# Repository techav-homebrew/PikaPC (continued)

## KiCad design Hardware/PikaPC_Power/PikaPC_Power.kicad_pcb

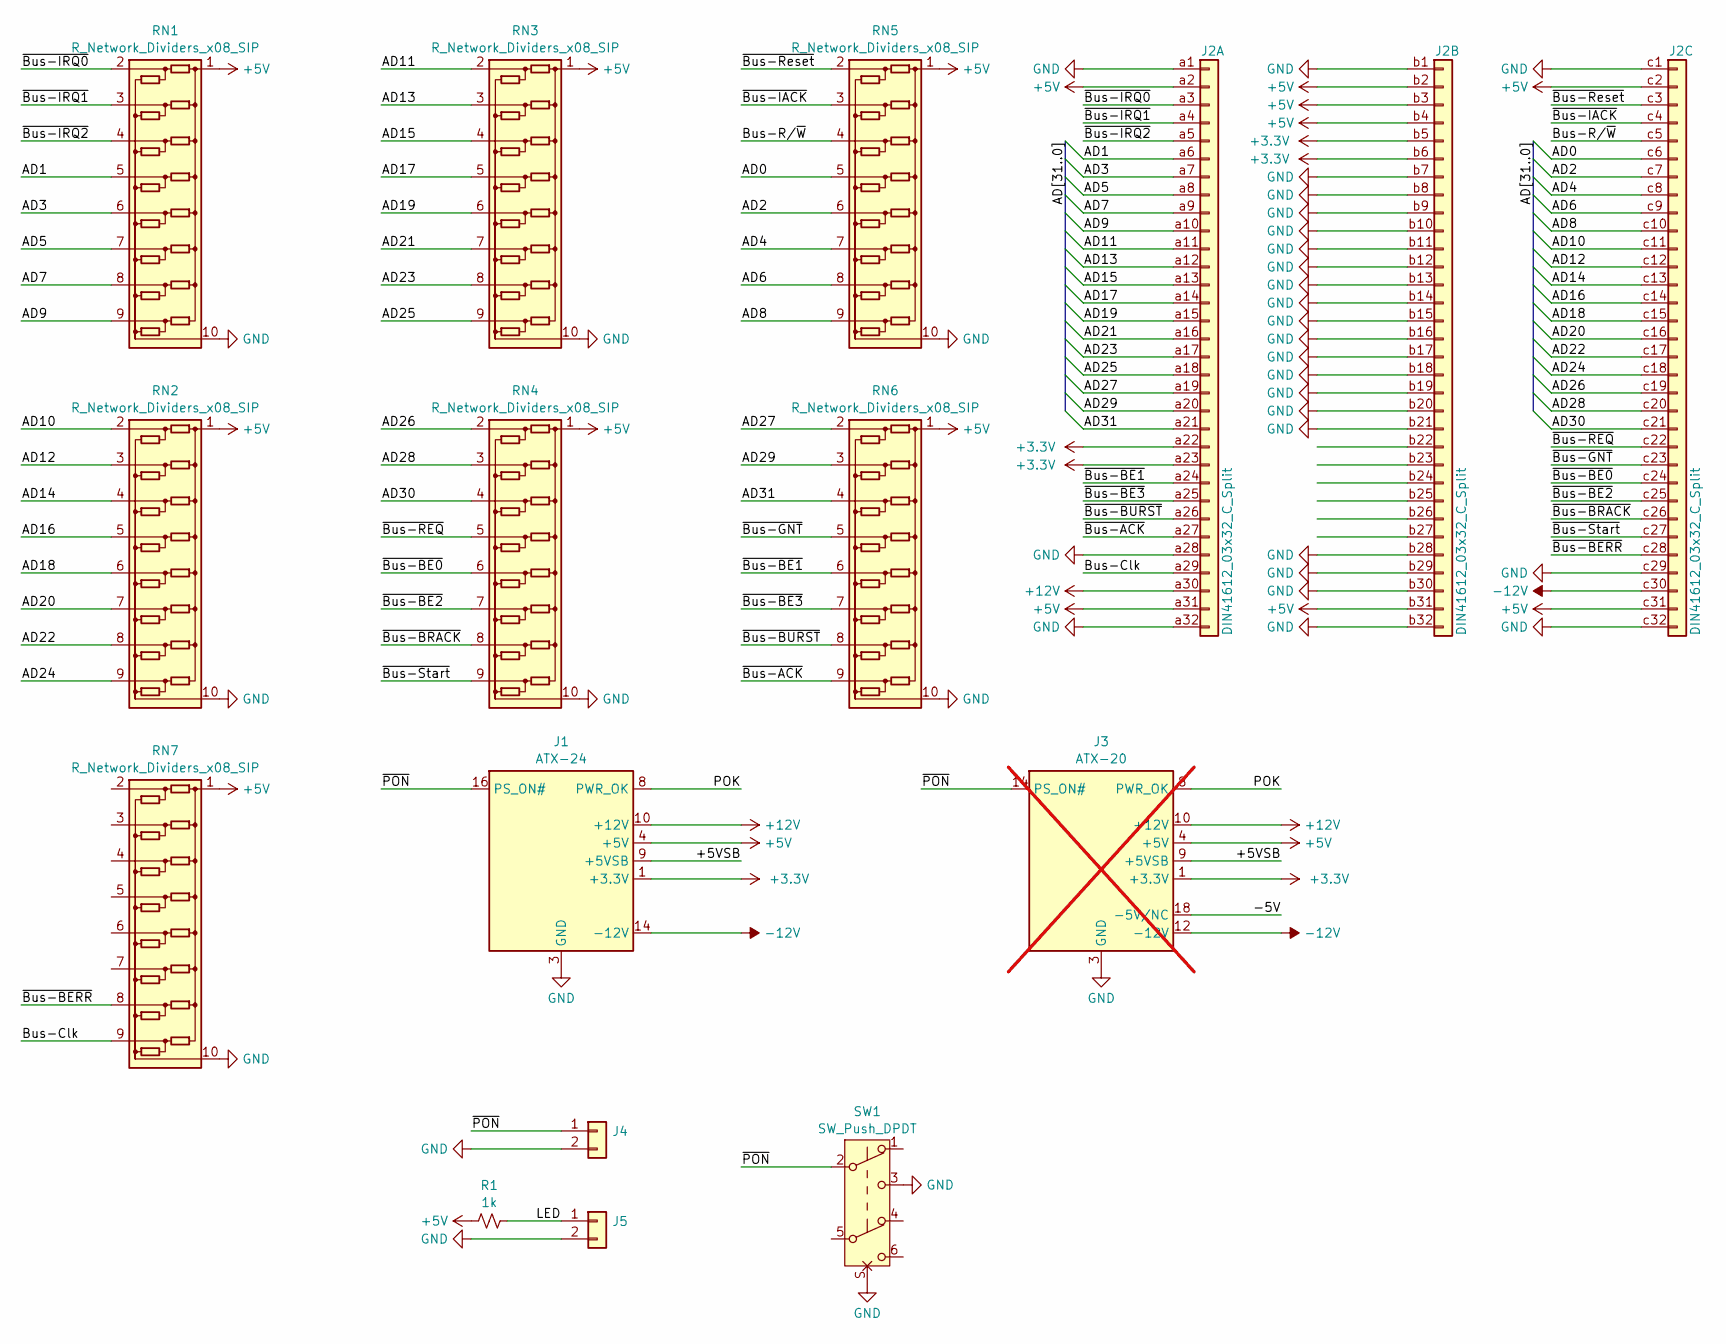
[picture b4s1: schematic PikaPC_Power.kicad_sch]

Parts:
J1: ATX-24; Molex_Mini-Fit_Jr_5569-24A2_2x12_P4.20mm_Horizontal
J2: DIN41612_03x32_C_Split; DIN41612_C_3x32_Male_Horizontal_THT
J3: ATX-20; Molex_Mini-Fit_Jr_5566-20A2_2x10_P4.20mm_Vertical; not fitted
J4, J5: Conn_01x02; PinHeader_1x02_P2.54mm_Vertical
R1: 1k; R_Axial_DIN0204_L3.6mm_D1.6mm_P7.62mm_Horizontal
RN1, RN2, RN3, RN4, RN5, RN6, RN7: R_Network_Dividers_x08_SIP; R_Array_SIP10
SW1: SW_Push_DPDT; SW_NKK_G1xJP

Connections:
+3.3V: J1.1 (+3.3V), J1.2 (+3.3V), J1.12 (+3.3V), J1.13 (+3.3V), J2.a22, J2.a23, J2.b5, J2.b6, J3.1 (+3.3V), J3.2 (+3.3V), J3.11 (+3.3V)
+5V: J1.4 (+5V), J1.6 (+5V), J1.21 (+5V), J1.22 (+5V), J1.23 (+5V), J2.a2, J2.a31, J2.b2, J2.b3, J2.b4, J2.b31, J2.c2, J2.c31, J3.4 (+5V), J3.6 (+5V), J3.19 (+5V), J3.20 (+5V), R1.1, RN1.1 (COM1), RN2.1 (COM1), RN3.1 (COM1), RN4.1 (COM1), RN5.1 (COM1), RN6.1 (COM1), RN7.1 (COM1)
+12V: J1.10 (+12V), J1.11 (+12V), J2.a30, J3.10 (+12V)
-12V: J1.14 (-12V), J2.c30, J3.12 (-12V)
/+5VSB: J1.9 (+5VSB), J3.9 (+5VSB)
/-5V: J3.18 (-5V/NC)
/AD0: J2.c6, RN5.5 (R4)
/AD1: J2.a6, RN1.5 (R4)
/AD2: J2.c7, RN5.6 (R5)
/AD3: J2.a7, RN1.6 (R5)
/AD4: J2.c8, RN5.7 (R6)
/AD5: J2.a8, RN1.7 (R6)
/AD6: J2.c9, RN5.8 (R7)
/AD7: J2.a9, RN1.8 (R7)
/AD8: J2.c10, RN5.9 (R8)
/AD9: J2.a10, RN1.9 (R8)
/AD10: J2.c11, RN2.2 (R1)
/AD11: J2.a11, RN3.2 (R1)
/AD12: J2.c12, RN2.3 (R2)
/AD13: J2.a12, RN3.3 (R2)
/AD14: J2.c13, RN2.4 (R3)
/AD15: J2.a13, RN3.4 (R3)
/AD16: J2.c14, RN2.5 (R4)
/AD17: J2.a14, RN3.5 (R4)
/AD18: J2.c15, RN2.6 (R5)
/AD19: J2.a15, RN3.6 (R5)
/AD20: J2.c16, RN2.7 (R6)
/AD21: J2.a16, RN3.7 (R6)
/AD22: J2.c17, RN2.8 (R7)
/AD23: J2.a17, RN3.8 (R7)
/AD24: J2.c18, RN2.9 (R8)
/AD25: J2.a18, RN3.9 (R8)
/AD26: J2.c19, RN4.2 (R1)
/AD27: J2.a19, RN6.2 (R1)
/AD28: J2.c20, RN4.3 (R2)
/AD29: J2.a20, RN6.3 (R2)
/AD30: J2.c21, RN4.4 (R3)
/AD31: J2.a21, RN6.4 (R3)
/Bus-Clk: J2.a29, RN7.9 (R8)
/Bus-R/~W: J2.c5, RN5.4 (R3)
/LED: J5.1, R1.2
/POK: J1.8 (PWR_OK), J3.8 (PWR_OK)
/~Bus-ACK: J2.a27, RN6.9 (R8)
/~Bus-BE0: J2.c24, RN4.6 (R5)
/~Bus-BE1: J2.a24, RN6.6 (R5)
/~Bus-BE2: J2.c25, RN4.7 (R6)
/~Bus-BE3: J2.a25, RN6.7 (R6)
/~Bus-BERR: J2.c28, RN7.8 (R7)
/~Bus-BRACK: J2.c26, RN4.8 (R7)
/~Bus-BURST: J2.a26, RN6.8 (R7)
/~Bus-GNT: J2.c23, RN6.5 (R4)
/~Bus-IACK: J2.c4, RN5.3 (R2)
/~Bus-IRQ0: J2.a3, RN1.2 (R1)
/~Bus-IRQ1: J2.a4, RN1.3 (R2)
/~Bus-IRQ2: J2.a5, RN1.4 (R3)
/~Bus-REQ: J2.c22, RN4.5 (R4)
/~Bus-Reset: J2.c3, RN5.2 (R1)
/~Bus-Start: J2.c27, RN4.9 (R8)
/~PON: J1.16 (PS_ON#), J3.14 (PS_ON#), J4.1, SW1.2 (B)
GND: J1.3 (GND), J1.5 (GND), J1.7 (GND), J1.15 (GND), J1.17 (GND), J1.18 (GND), J1.19 (GND), J1.24 (GND), J2.a1, J2.a28, J2.a32, J2.b1, J2.b7, J2.b8, J2.b9, J2.b10, J2.b11, J2.b12, J2.b13, J2.b14, J2.b15, J2.b16, J2.b17, J2.b18, J2.b19, J2.b20, J2.b21, J2.b28, J2.b29, J2.b30, J2.b32, J2.c1, J2.c29, J2.c32, J3.3 (GND), J3.5 (GND), J3.7 (GND), J3.13 (GND), J3.15 (GND), J3.16 (GND), J3.17 (GND), J4.2, J5.2, RN1.10 (COM2), RN2.10 (COM2), RN3.10 (COM2), RN4.10 (COM2), RN5.10 (COM2), RN6.10 (COM2), RN7.10 (COM2), SW1.3 (C), SW1.S

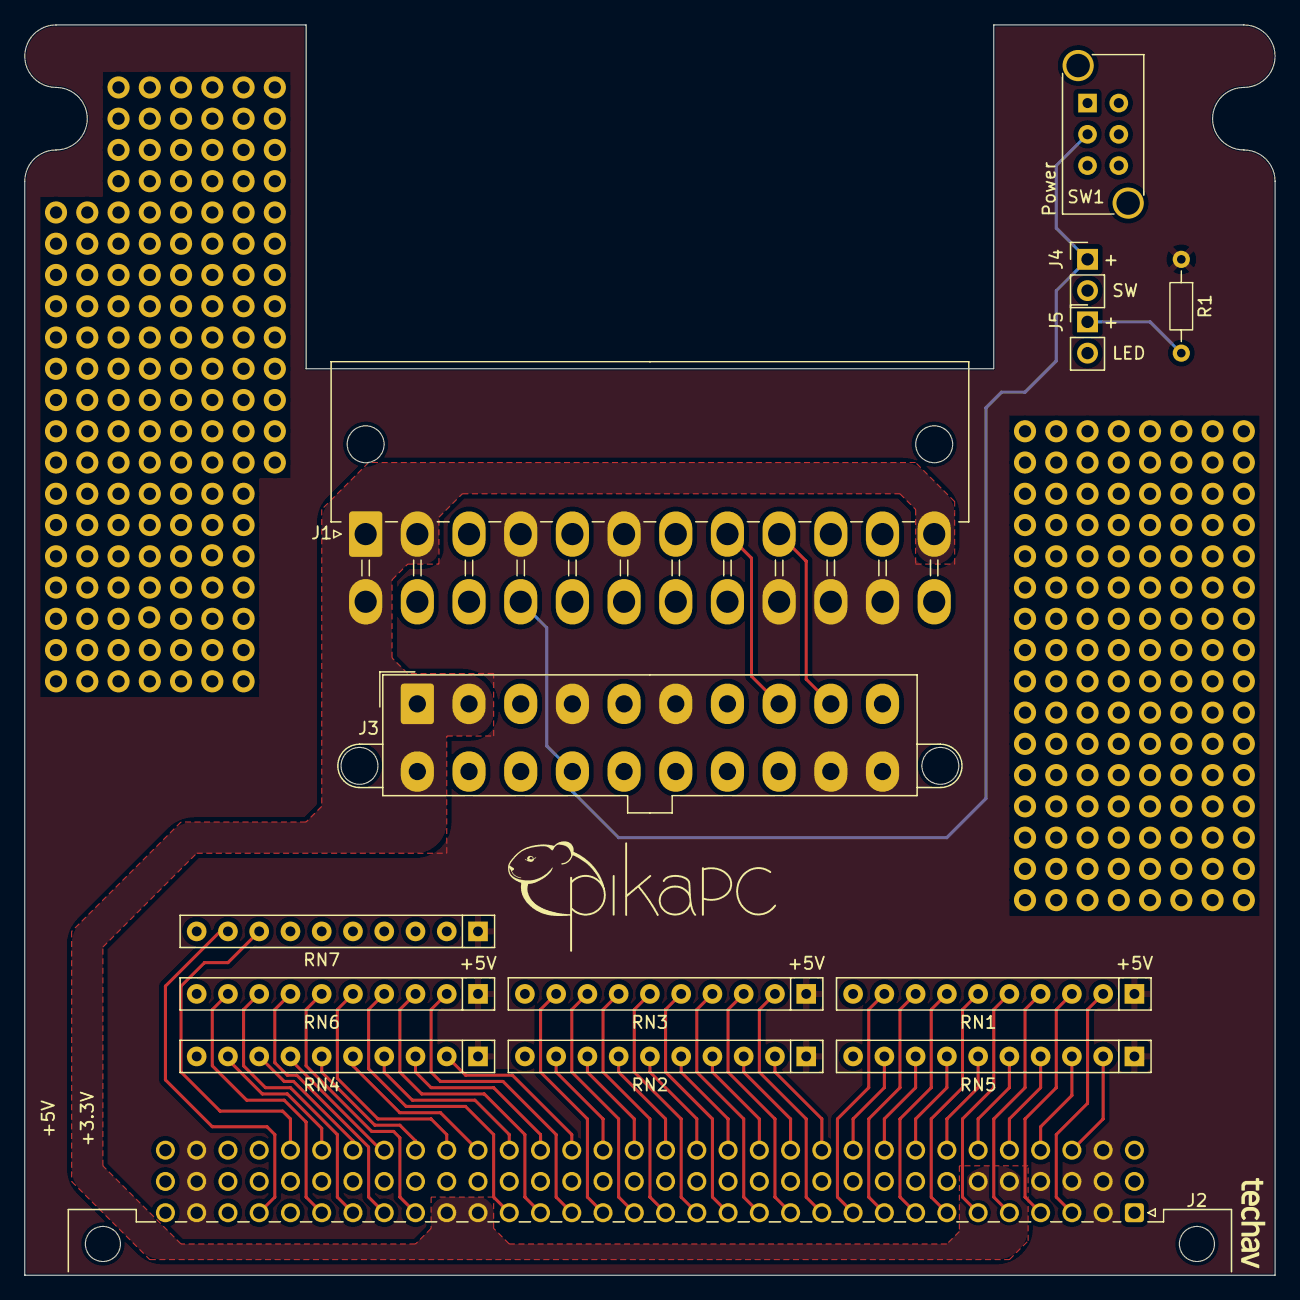
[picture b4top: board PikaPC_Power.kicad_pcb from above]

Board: 2 copper layers, 101.6 x 101.6 mm, 14 parts (0 on the bottom side), 59 nets.

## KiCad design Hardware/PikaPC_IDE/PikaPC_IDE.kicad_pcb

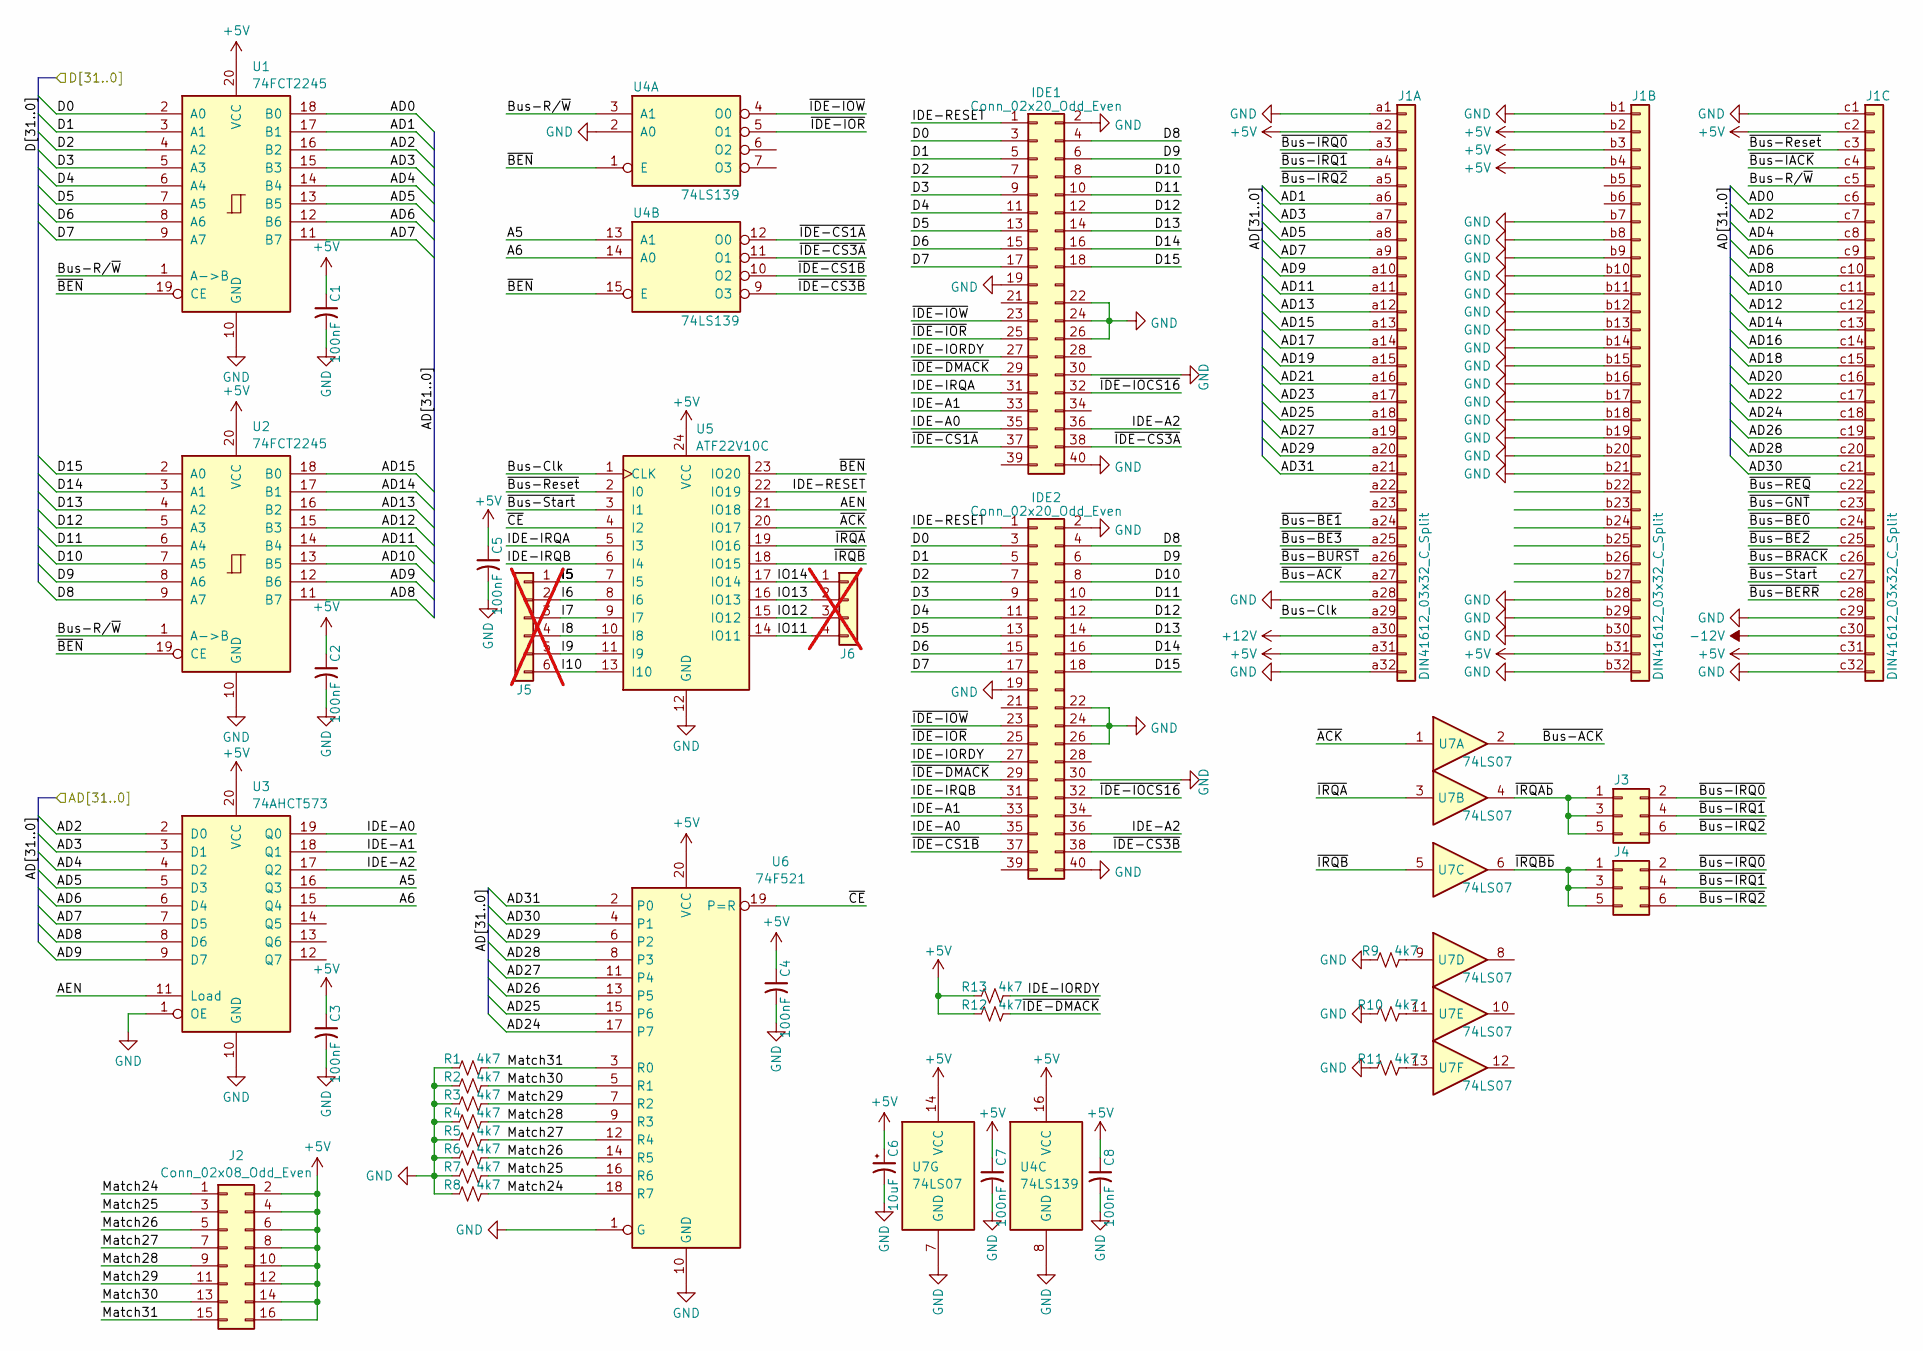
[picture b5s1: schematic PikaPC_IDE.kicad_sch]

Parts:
C1, C2, C3, C4, C5, C7, C8: 100nF; C_0805_2012Metric; Mouser 187-CL21B104KACNNNC
C6: 10uF; CP_Elec_4x5.7; Mouser 80-EDK106M016A9BAA
IDE1, IDE2: Conn_02x20_Odd_Even; IDC-Header_2x20_P2.54mm_Vertical; Mouser-Part 710-61203921621
J1: DIN41612_03x32_C_Split; DIN41612_C_3x32_Male_Horizontal_THT
J2: Conn_02x08_Odd_Even; PinHeader_2x08_P2.54mm_Vertical
J3, J4: Conn_02x03_Odd_Even; PinHeader_2x03_P2.54mm_Vertical
J5: Conn_01x06; PinHeader_1x06_P2.54mm_Vertical; not fitted
J6: Conn_01x04; PinHeader_1x04_P2.54mm_Vertical; not fitted
R1, R2, R3, R4, R5, R6, R7, R8, R9, R10, R11, R12, R13: 4k7; R_0805_2012Metric; Mouser 303-0805W8J0472T5E
U1, U2: 74FCT2245; SOIC-20W_7.5x12.8mm_P1.27mm; Mouser 595-CY74FCT2245TSOCT
U3: 74AHCT573; TSSOP-20_4.4x6.5mm_P0.65mm; Mouser 771-74AHCT573PW-T
U4: 74LS139; DIP-16_W7.62mm_Socket
U5: ATF22V10C; DIP-24_W7.62mm_Socket; Mouser 556-ATF22V10C-10PU
U6: 74F521; SOIC-20W_7.5x12.8mm_P1.27mm; Mouser 595-SN74F521DWR
U7: 74LS07; DIP-14_W7.62mm_Socket; Mouser 595-SN74LS07N

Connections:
+5V: C1.1, C2.1, C3.1, C4.1, C5.1, C6.1, C7.1, C8.1, J1.a2, J1.a31, J1.b2, J1.b3, J1.b4, J1.b31, J1.c2, J1.c31, J2.2, J2.4, J2.6, J2.8, J2.10, J2.12, J2.14, J2.16, R12.1, R13.1, U1.20 (VCC), U2.20 (VCC), U3.20 (VCC), U4.16 (VCC), U5.24 (VCC), U6.20 (VCC), U7.14 (VCC)
+12V: J1.a30
-12V: J1.c30
/A5: U3.16 (Q3), U4.13 (A1)
/A6: U3.15 (Q4), U4.14 (A0)
/AD0: J1.c6, U1.18 (B0)
/AD1: J1.a6, U1.17 (B1)
/AD2: J1.c7, U1.16 (B2), U3.2 (D0)
/AD3: J1.a7, U1.15 (B3), U3.3 (D1)
/AD4: J1.c8, U1.14 (B4), U3.4 (D2)
/AD5: J1.a8, U1.13 (B5), U3.5 (D3)
/AD6: J1.c9, U1.12 (B6), U3.6 (D4)
/AD7: J1.a9, U1.11 (B7), U3.7 (D5)
/AD8: J1.c10, U2.11 (B7), U3.8 (D6)
/AD9: J1.a10, U2.12 (B6), U3.9 (D7)
/AD10: J1.c11, U2.13 (B5)
/AD11: J1.a11, U2.14 (B4)
/AD12: J1.c12, U2.15 (B3)
/AD13: J1.a12, U2.16 (B2)
/AD14: J1.c13, U2.17 (B1)
/AD15: J1.a13, U2.18 (B0)
/AD16: J1.c14
/AD17: J1.a14
/AD18: J1.c15
/AD19: J1.a15
/AD20: J1.c16
/AD21: J1.a16
/AD22: J1.c17
/AD23: J1.a17
/AD24: J1.c18, U6.17 (P7)
/AD25: J1.a18, U6.15 (P6)
/AD26: J1.c19, U6.13 (P5)
/AD27: J1.a19, U6.11 (P4)
/AD28: J1.c20, U6.8 (P3)
/AD29: J1.a20, U6.6 (P2)
/AD30: J1.c21, U6.4 (P1)
/AD31: J1.a21, U6.2 (P0)
/AEN: U3.11 (Load), U5.21 (IO18)
/Bus-Clk: J1.a29, U5.1 (CLK)
/Bus-R/~W: J1.c5, U1.1 (A->B), U2.1 (A->B), U4.3 (A1)
/D0: IDE1.3, IDE2.3, U1.2 (A0)
/D1: IDE1.5, IDE2.5, U1.3 (A1)
/D2: IDE1.7, IDE2.7, U1.4 (A2)
/D3: IDE1.9, IDE2.9, U1.5 (A3)
/D4: IDE1.11, IDE2.11, U1.6 (A4)
/D5: IDE1.13, IDE2.13, U1.7 (A5)
/D6: IDE1.15, IDE2.15, U1.8 (A6)
/D7: IDE1.17, IDE2.17, U1.9 (A7)
/D8: IDE1.4, IDE2.4, U2.9 (A7)
/D9: IDE1.6, IDE2.6, U2.8 (A6)
/D10: IDE1.8, IDE2.8, U2.7 (A5)
/D11: IDE1.10, IDE2.10, U2.6 (A4)
/D12: IDE1.12, IDE2.12, U2.5 (A3)
/D13: IDE1.14, IDE2.14, U2.4 (A2)
/D14: IDE1.16, IDE2.16, U2.3 (A1)
/D15: IDE1.18, IDE2.18, U2.2 (A0)
/I5: J5.1, U5.7 (I5)
/I6: J5.2, U5.8 (I6)
/I7: J5.3, U5.9 (I7)
/I8: J5.4, U5.10 (I8)
/I9: J5.5, U5.11 (I9)
/I10: J5.6, U5.13 (I10)
/IDE-A0: IDE1.35, IDE2.35, U3.19 (Q0)
/IDE-A1: IDE1.33, IDE2.33, U3.18 (Q1)
/IDE-A2: IDE1.36, IDE2.36, U3.17 (Q2)
/IDE-IORDY: IDE1.27, IDE2.27, R13.2
/IDE-IRQA: IDE1.31, U5.5 (I3)
/IDE-IRQB: IDE2.31, U5.6 (I4)
/IDE-RESET: IDE1.1, IDE2.1, U5.22 (IO19)
/IO11: J6.4, U5.14 (IO11)
/IO12: J6.3, U5.15 (IO12)
/IO13: J6.2, U5.16 (IO13)
/IO14: J6.1, U5.17 (IO14)
/Match24: J2.1, R8.2, U6.18 (R7)
/Match25: J2.3, R7.2, U6.16 (R6)
/Match26: J2.5, R6.2, U6.14 (R5)
/Match27: J2.7, R5.2, U6.12 (R4)
/Match28: J2.9, R4.2, U6.9 (R3)
/Match29: J2.11, R3.2, U6.7 (R2)
/Match30: J2.13, R2.2, U6.5 (R1)
/Match31: J2.15, R1.2, U6.3 (R0)
/~ACK: U5.20 (IO17), U7.1
/~BEN: U1.19 (CE), U2.19 (CE), U4.1 (E), U4.15 (E), U5.23 (IO20)
/~Bus-ACK: J1.a27, U7.2
/~Bus-BE0: J1.c24
/~Bus-BE1: J1.a24
/~Bus-BE2: J1.c25
/~Bus-BE3: J1.a25
/~Bus-BERR: J1.c28
/~Bus-BRACK: J1.c26
/~Bus-BURST: J1.a26
/~Bus-GNT: J1.c23
/~Bus-IACK: J1.c4
/~Bus-IRQ0: J1.a3, J3.2, J4.2
/~Bus-IRQ1: J1.a4, J3.4, J4.4
/~Bus-IRQ2: J1.a5, J3.6, J4.6
/~Bus-REQ: J1.c22
/~Bus-Reset: J1.c3, U5.2 (I0)
/~Bus-Start: J1.c27, U5.3 (I1)
/~CE: U5.4 (I2), U6.19 (P=R)
/~IDE-CS1A: IDE1.37, U4.12 (O0)
/~IDE-CS1B: IDE2.37, U4.10 (O2)
/~IDE-CS3A: IDE1.38, U4.11 (O1)
/~IDE-CS3B: IDE2.38, U4.9 (O3)
/~IDE-DMACK: IDE1.29, IDE2.29, R12.2
/~IDE-IOCS16: IDE1.32, IDE2.32
/~IDE-IOR: IDE1.25, IDE2.25, U4.5 (O1)
/~IDE-IOW: IDE1.23, IDE2.23, U4.4 (O0)
/~IRQAb: J3.1, J3.3, J3.5, U7.4
/~IRQA: U5.19 (IO16), U7.3
/~IRQBb: J4.1, J4.3, J4.5, U7.6
/~IRQB: U5.18 (IO15), U7.5
GND: C1.2, C2.2, C3.2, C4.2, C5.2, C6.2, C7.2, C8.2, IDE1.2, IDE1.19, IDE1.22, IDE1.24, IDE1.26, IDE1.30, IDE1.40, IDE2.2, IDE2.19, IDE2.22, IDE2.24, IDE2.26, IDE2.30, IDE2.40, J1.a1, J1.a28, J1.a32, J1.b1, J1.b7, J1.b8, J1.b9, J1.b10, J1.b11, J1.b12, J1.b13, J1.b14, J1.b15, J1.b16, J1.b17, J1.b18, J1.b19, J1.b20, J1.b21, J1.b28, J1.b29, J1.b30, J1.b32, J1.c1, J1.c29, J1.c32, R1.1, R2.1, R3.1, R4.1, R5.1, R6.1, R7.1, R8.1, R9.1, R10.1, R11.1, U1.10 (GND), U2.10 (GND), U3.1 (OE), U3.10 (GND), U4.2 (A0), U4.8 (GND), U5.12 (GND), U6.1 (G), U6.10 (GND), U7.7 (GND)
unnamed: R9.2, U7.9
unnamed: R10.2, U7.11
unnamed: R11.2, U7.13

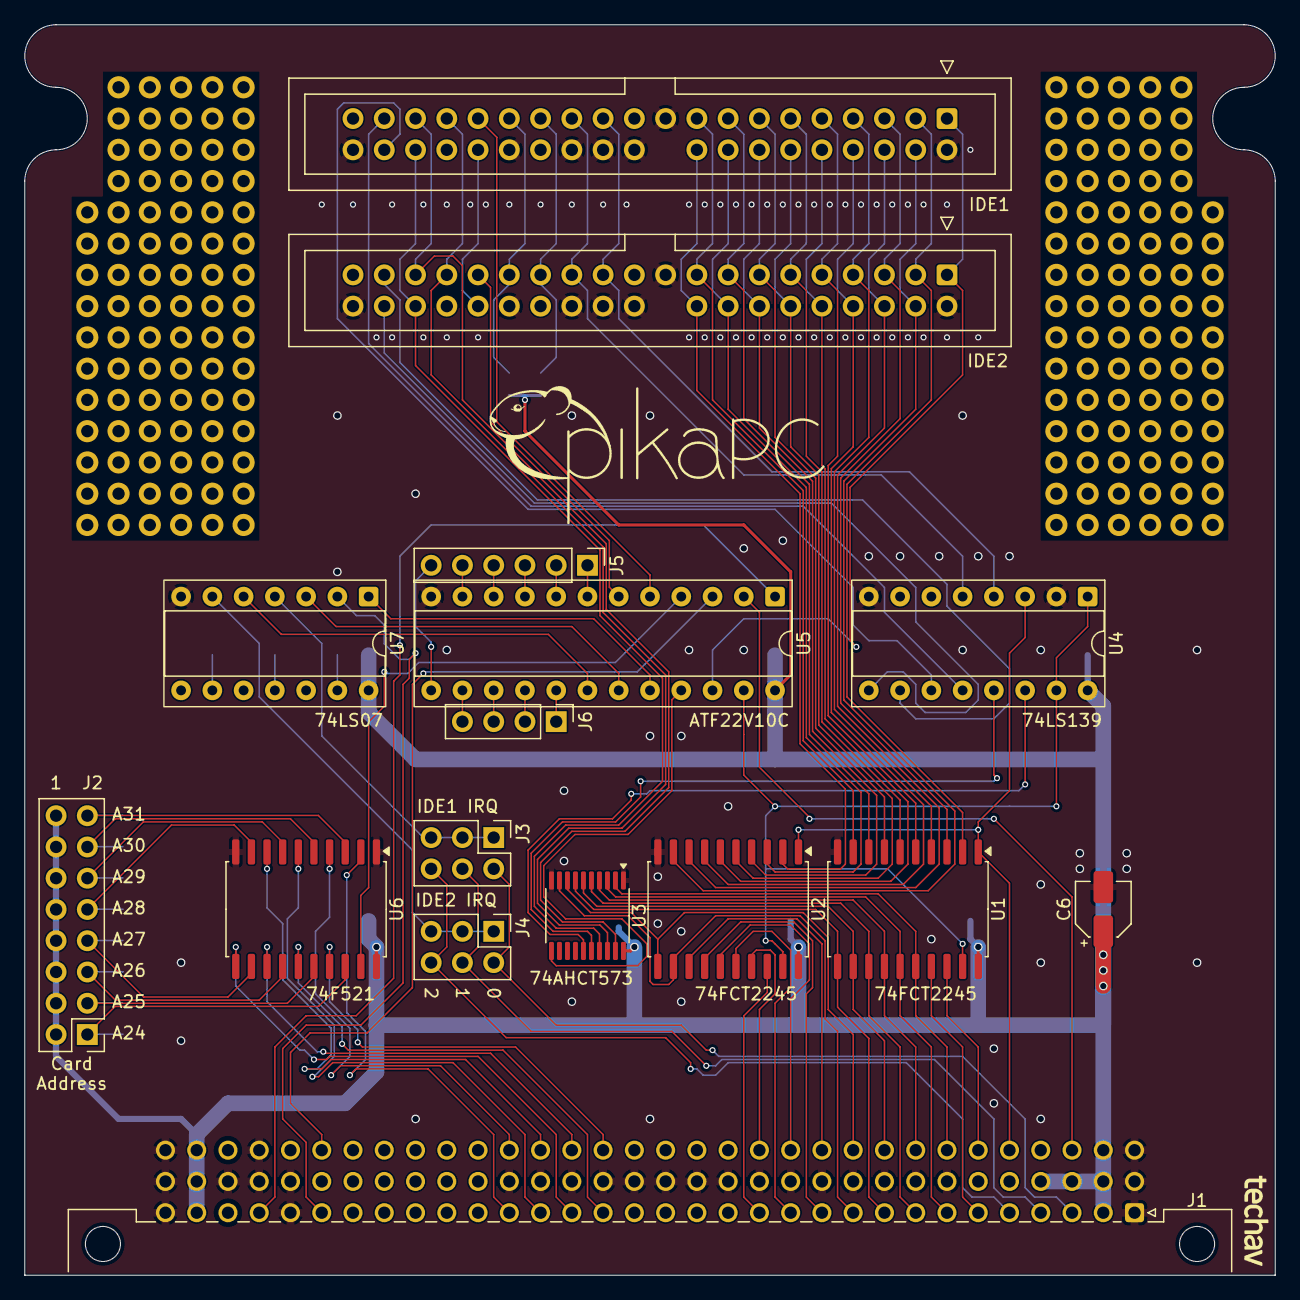
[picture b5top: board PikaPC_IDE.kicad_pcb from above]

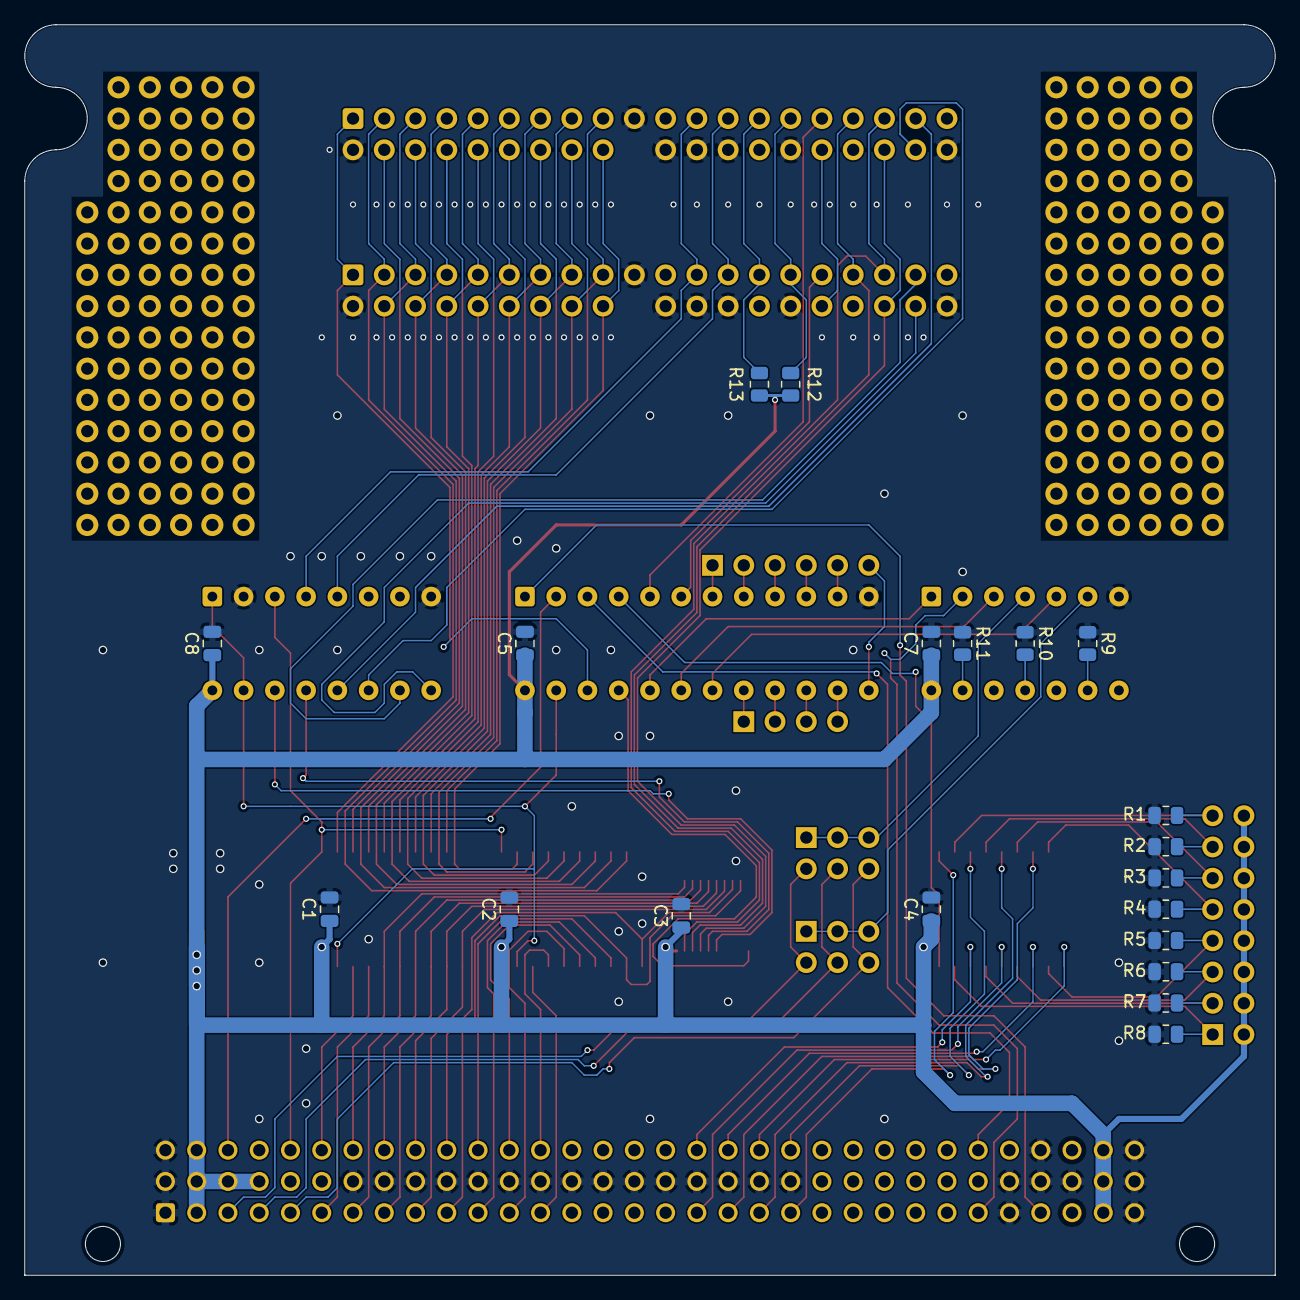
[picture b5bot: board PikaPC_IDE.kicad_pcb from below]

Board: 2 copper layers, 101.6 x 101.6 mm, 36 parts (20 on the bottom side), 96 nets.

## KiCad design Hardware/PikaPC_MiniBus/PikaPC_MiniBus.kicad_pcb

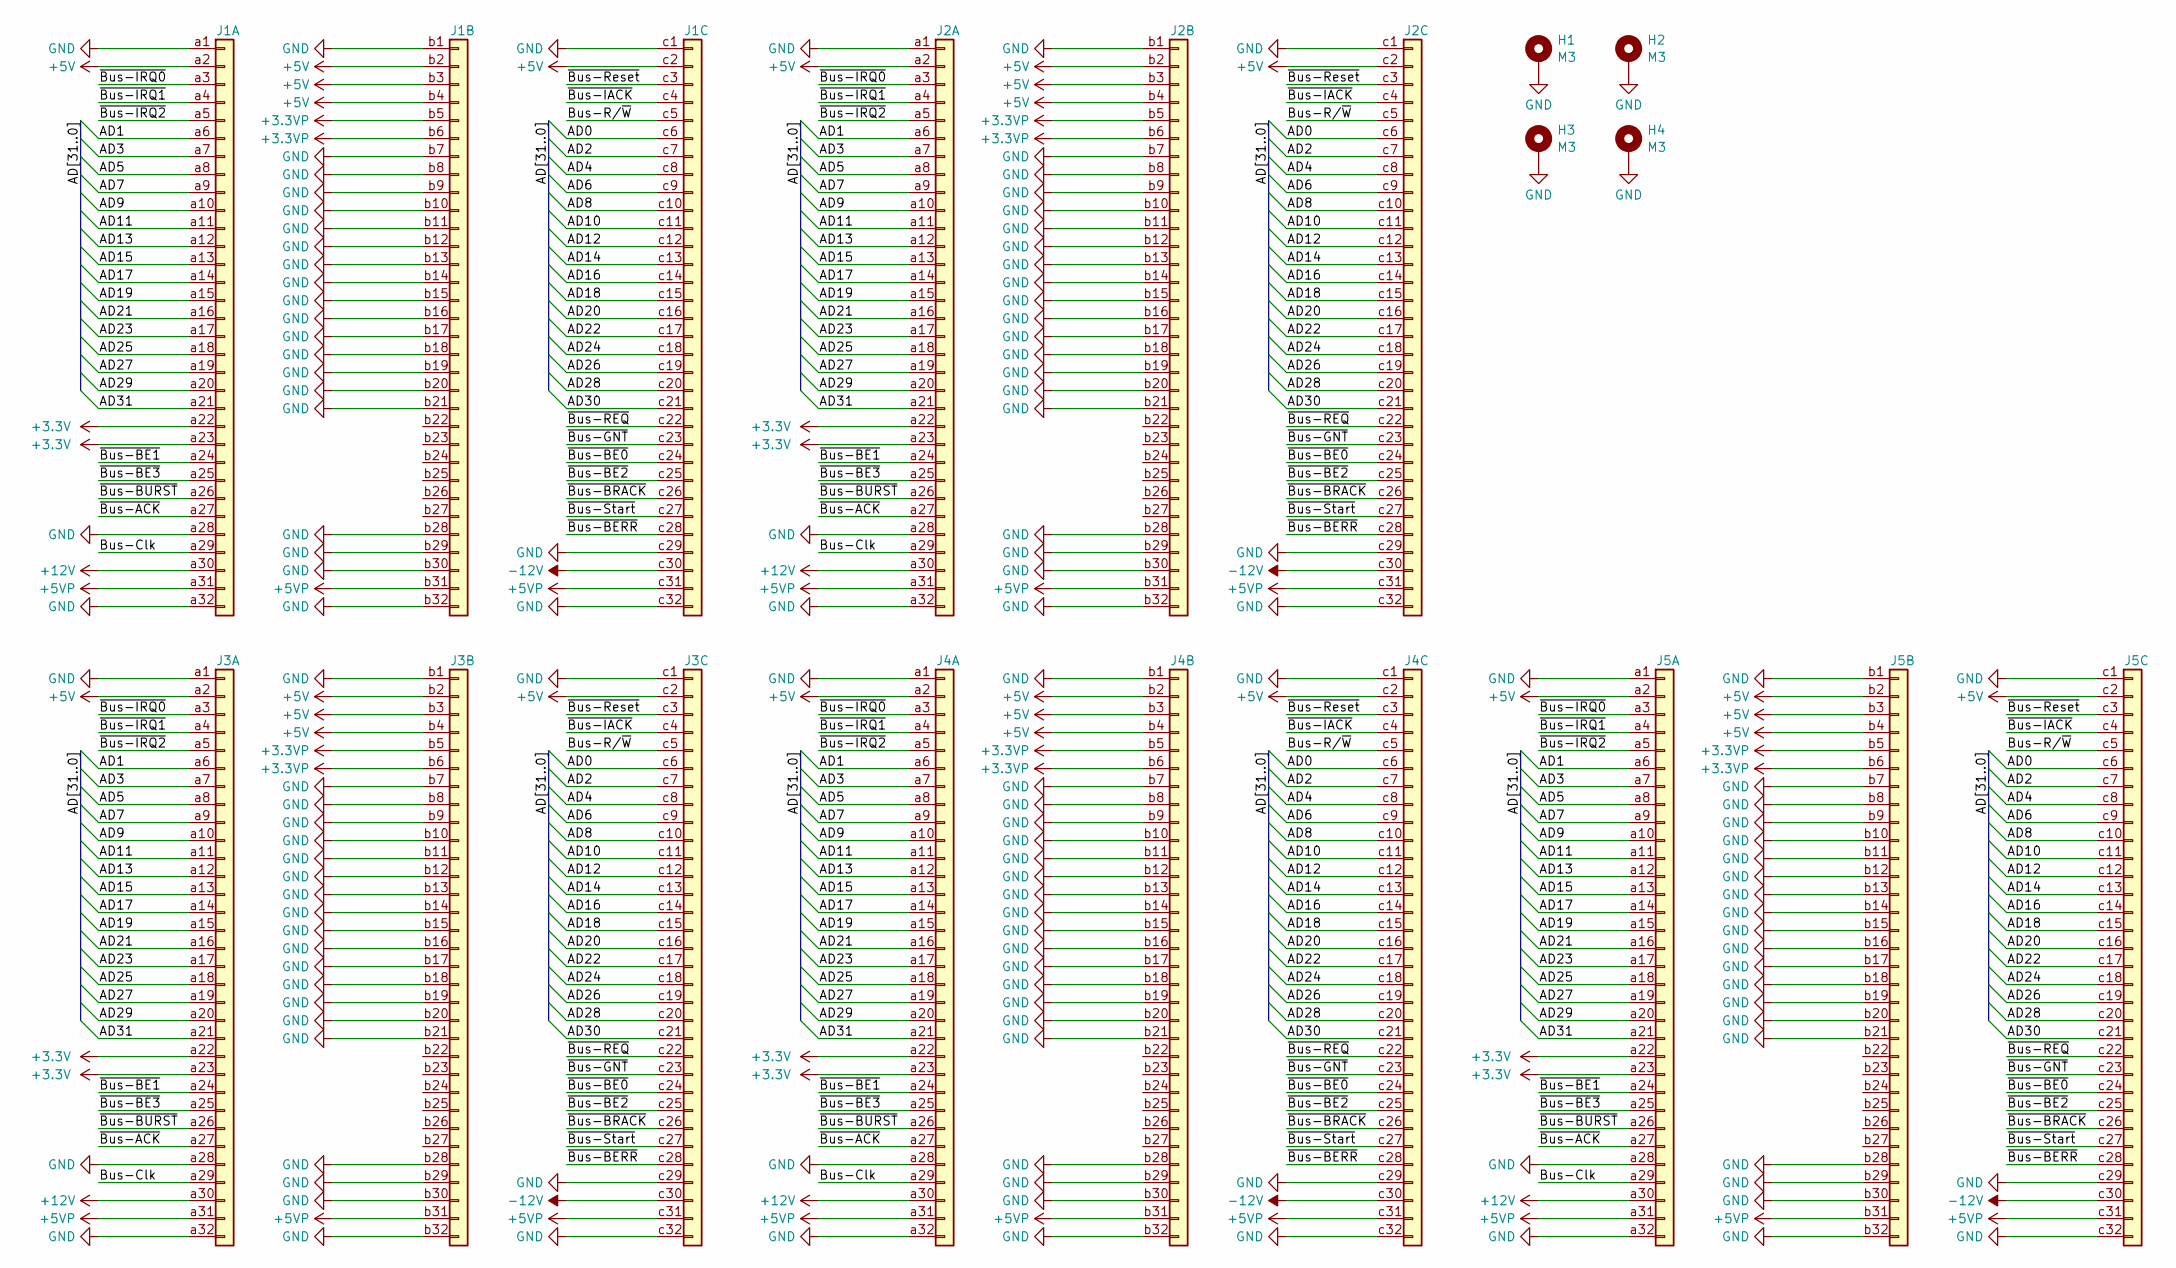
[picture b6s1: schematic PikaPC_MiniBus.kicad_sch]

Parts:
H1, H2, H3, H4: M3; MountingHole_3.2mm_M3_Pad_Via
J1, J2, J3, J4, J5: DIN41612_03x32_C_Split; DIN41612_C_3x32_Female_Vertical_THT

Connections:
+3.3V: J1.a22, J1.a23, J2.a22, J2.a23, J3.a22, J3.a23, J4.a22, J4.a23, J5.a22, J5.a23
+3.3VP: J1.b5, J1.b6, J2.b5, J2.b6, J3.b5, J3.b6, J4.b5, J4.b6, J5.b5, J5.b6
+5V: J1.a2, J1.b2, J1.b3, J1.b4, J1.c2, J2.a2, J2.b2, J2.b3, J2.b4, J2.c2, J3.a2, J3.b2, J3.b3, J3.b4, J3.c2, J4.a2, J4.b2, J4.b3, J4.b4, J4.c2, J5.a2, J5.b2, J5.b3, J5.b4, J5.c2
+5VP: J1.a31, J1.b31, J1.c31, J2.a31, J2.b31, J2.c31, J3.a31, J3.b31, J3.c31, J4.a31, J4.b31, J4.c31, J5.a31, J5.b31, J5.c31
+12V: J1.a30, J2.a30, J3.a30, J4.a30, J5.a30
-12V: J1.c30, J2.c30, J3.c30, J4.c30, J5.c30
/AD0: J1.c6, J2.c6, J3.c6, J4.c6, J5.c6
/AD1: J1.a6, J2.a6, J3.a6, J4.a6, J5.a6
/AD2: J1.c7, J2.c7, J3.c7, J4.c7, J5.c7
/AD3: J1.a7, J2.a7, J3.a7, J4.a7, J5.a7
/AD4: J1.c8, J2.c8, J3.c8, J4.c8, J5.c8
/AD5: J1.a8, J2.a8, J3.a8, J4.a8, J5.a8
/AD6: J1.c9, J2.c9, J3.c9, J4.c9, J5.c9
/AD7: J1.a9, J2.a9, J3.a9, J4.a9, J5.a9
/AD8: J1.c10, J2.c10, J3.c10, J4.c10, J5.c10
/AD9: J1.a10, J2.a10, J3.a10, J4.a10, J5.a10
/AD10: J1.c11, J2.c11, J3.c11, J4.c11, J5.c11
/AD11: J1.a11, J2.a11, J3.a11, J4.a11, J5.a11
/AD12: J1.c12, J2.c12, J3.c12, J4.c12, J5.c12
/AD13: J1.a12, J2.a12, J3.a12, J4.a12, J5.a12
/AD14: J1.c13, J2.c13, J3.c13, J4.c13, J5.c13
/AD15: J1.a13, J2.a13, J3.a13, J4.a13, J5.a13
/AD16: J1.c14, J2.c14, J3.c14, J4.c14, J5.c14
/AD17: J1.a14, J2.a14, J3.a14, J4.a14, J5.a14
/AD18: J1.c15, J2.c15, J3.c15, J4.c15, J5.c15
/AD19: J1.a15, J2.a15, J3.a15, J4.a15, J5.a15
/AD20: J1.c16, J2.c16, J3.c16, J4.c16, J5.c16
/AD21: J1.a16, J2.a16, J3.a16, J4.a16, J5.a16
/AD22: J1.c17, J2.c17, J3.c17, J4.c17, J5.c17
/AD23: J1.a17, J2.a17, J3.a17, J4.a17, J5.a17
/AD24: J1.c18, J2.c18, J3.c18, J4.c18, J5.c18
/AD25: J1.a18, J2.a18, J3.a18, J4.a18, J5.a18
/AD26: J1.c19, J2.c19, J3.c19, J4.c19, J5.c19
/AD27: J1.a19, J2.a19, J3.a19, J4.a19, J5.a19
/AD28: J1.c20, J2.c20, J3.c20, J4.c20, J5.c20
/AD29: J1.a20, J2.a20, J3.a20, J4.a20, J5.a20
/AD30: J1.c21, J2.c21, J3.c21, J4.c21, J5.c21
/AD31: J1.a21, J2.a21, J3.a21, J4.a21, J5.a21
/Bus-Clk: J1.a29, J2.a29, J3.a29, J4.a29, J5.a29
/Bus-R/~W: J1.c5, J2.c5, J3.c5, J4.c5, J5.c5
/~Bus-ACK: J1.a27, J2.a27, J3.a27, J4.a27, J5.a27
/~Bus-BE0: J1.c24, J2.c24, J3.c24, J4.c24, J5.c24
/~Bus-BE1: J1.a24, J2.a24, J3.a24, J4.a24, J5.a24
/~Bus-BE2: J1.c25, J2.c25, J3.c25, J4.c25, J5.c25
/~Bus-BE3: J1.a25, J2.a25, J3.a25, J4.a25, J5.a25
/~Bus-BERR: J1.c28, J2.c28, J3.c28, J4.c28, J5.c28
/~Bus-BRACK: J1.c26, J2.c26, J3.c26, J4.c26, J5.c26
/~Bus-BURST: J1.a26, J2.a26, J3.a26, J4.a26, J5.a26
/~Bus-GNT: J1.c23, J2.c23, J3.c23, J4.c23, J5.c23
/~Bus-IACK: J1.c4, J2.c4, J3.c4, J4.c4, J5.c4
/~Bus-IRQ0: J1.a3, J2.a3, J3.a3, J4.a3, J5.a3
/~Bus-IRQ1: J1.a4, J2.a4, J3.a4, J4.a4, J5.a4
/~Bus-IRQ2: J1.a5, J2.a5, J3.a5, J4.a5, J5.a5
/~Bus-REQ: J1.c22, J2.c22, J3.c22, J4.c22, J5.c22
/~Bus-Reset: J1.c3, J2.c3, J3.c3, J4.c3, J5.c3
/~Bus-Start: J1.c27, J2.c27, J3.c27, J4.c27, J5.c27
GND: H1.1, H2.1, H3.1, H4.1, J1.a1, J1.a28, J1.a32, J1.b1, J1.b7, J1.b8, J1.b9, J1.b10, J1.b11, J1.b12, J1.b13, J1.b14, J1.b15, J1.b16, J1.b17, J1.b18, J1.b19, J1.b20, J1.b21, J1.b28, J1.b29, J1.b30, J1.b32, J1.c1, J1.c29, J1.c32, J2.a1, J2.a28, J2.a32, J2.b1, J2.b7, J2.b8, J2.b9, J2.b10, J2.b11, J2.b12, J2.b13, J2.b14, J2.b15, J2.b16, J2.b17, J2.b18, J2.b19, J2.b20, J2.b21, J2.b28, J2.b29, J2.b30, J2.b32, J2.c1, J2.c29, J2.c32, J3.a1, J3.a28, J3.a32, J3.b1, J3.b7, J3.b8, J3.b9, J3.b10, J3.b11, J3.b12, J3.b13, J3.b14, J3.b15, J3.b16, J3.b17, J3.b18, J3.b19, J3.b20, J3.b21, J3.b28, J3.b29, J3.b30, J3.b32, J3.c1, J3.c29, J3.c32, J4.a1, J4.a28, J4.a32, J4.b1, J4.b7, J4.b8, J4.b9, J4.b10, J4.b11, J4.b12, J4.b13, J4.b14, J4.b15, J4.b16, J4.b17, J4.b18, J4.b19, J4.b20, J4.b21, J4.b28, J4.b29, J4.b30, J4.b32, J4.c1, J4.c29, J4.c32, J5.a1, J5.a28, J5.a32, J5.b1, J5.b7, J5.b8, J5.b9, J5.b10, J5.b11, J5.b12, J5.b13, J5.b14, J5.b15, J5.b16, J5.b17, J5.b18, J5.b19, J5.b20, J5.b21, J5.b28, J5.b29, J5.b30, J5.b32, J5.c1, J5.c29, J5.c32

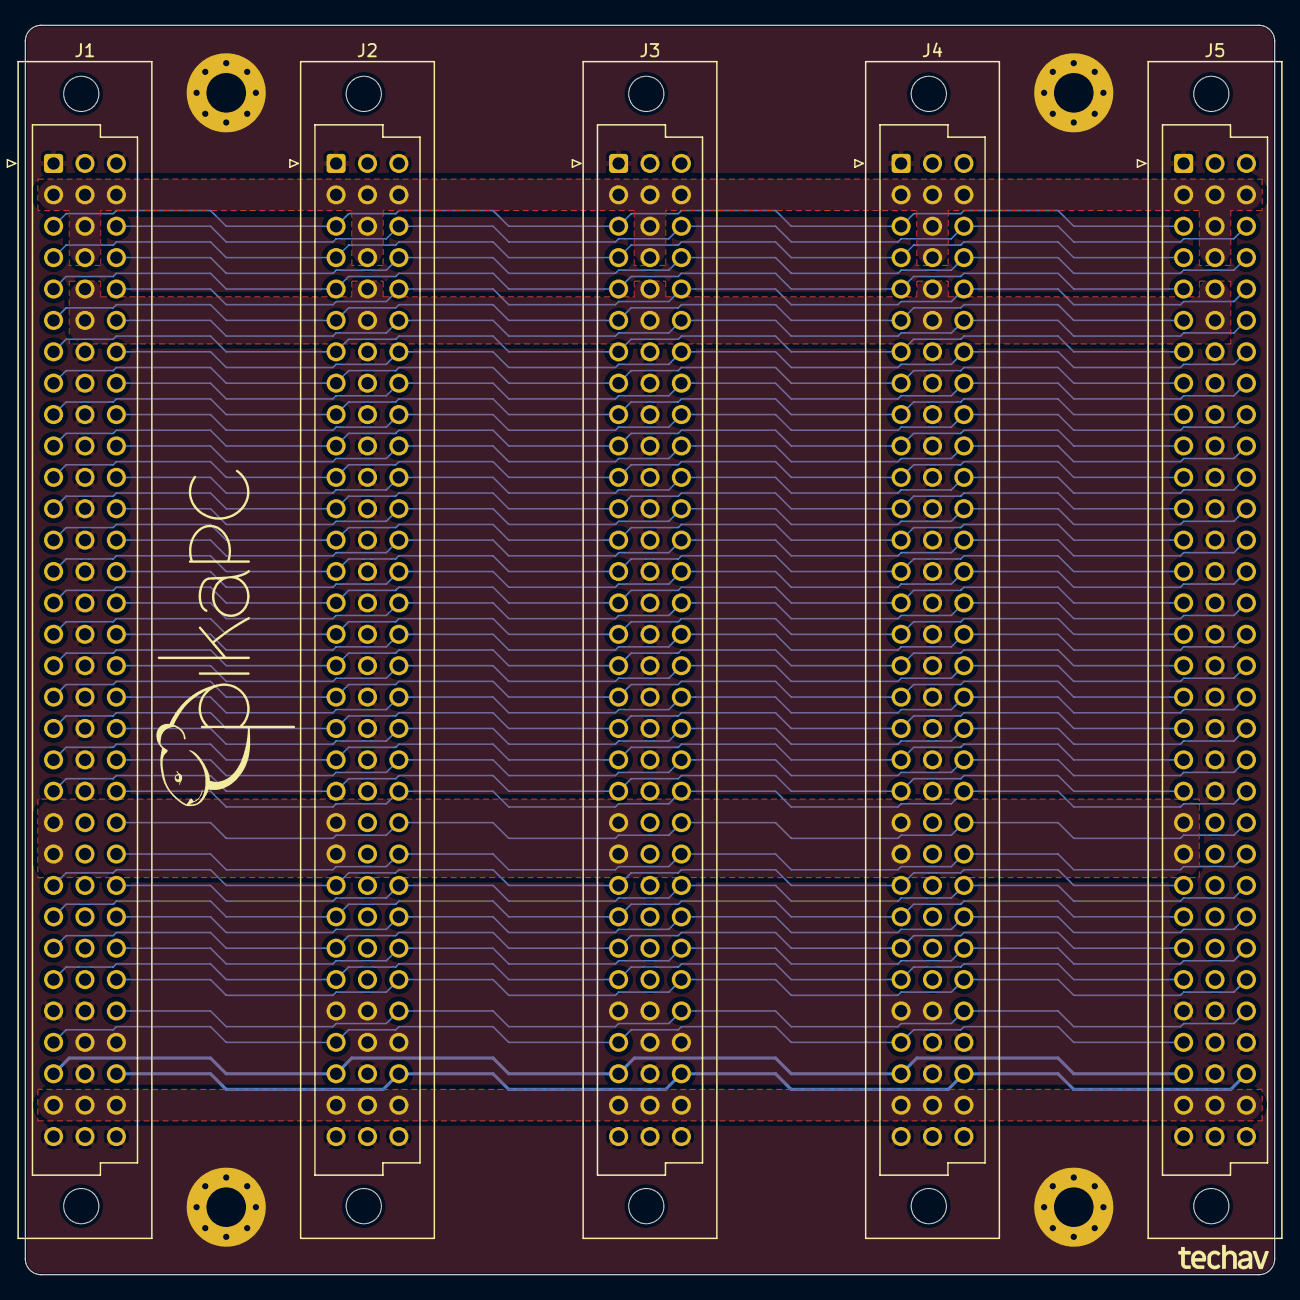
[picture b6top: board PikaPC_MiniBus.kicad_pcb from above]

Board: 2 copper layers, 101.1 x 101.1 mm, 9 parts (0 on the bottom side), 57 nets.
